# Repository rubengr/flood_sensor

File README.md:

# Flood Sensor 

## Pictures

## 3D

## Author
@2020
[Rúben Rodrigues](mailto:ruben_gr@live.com.pt)

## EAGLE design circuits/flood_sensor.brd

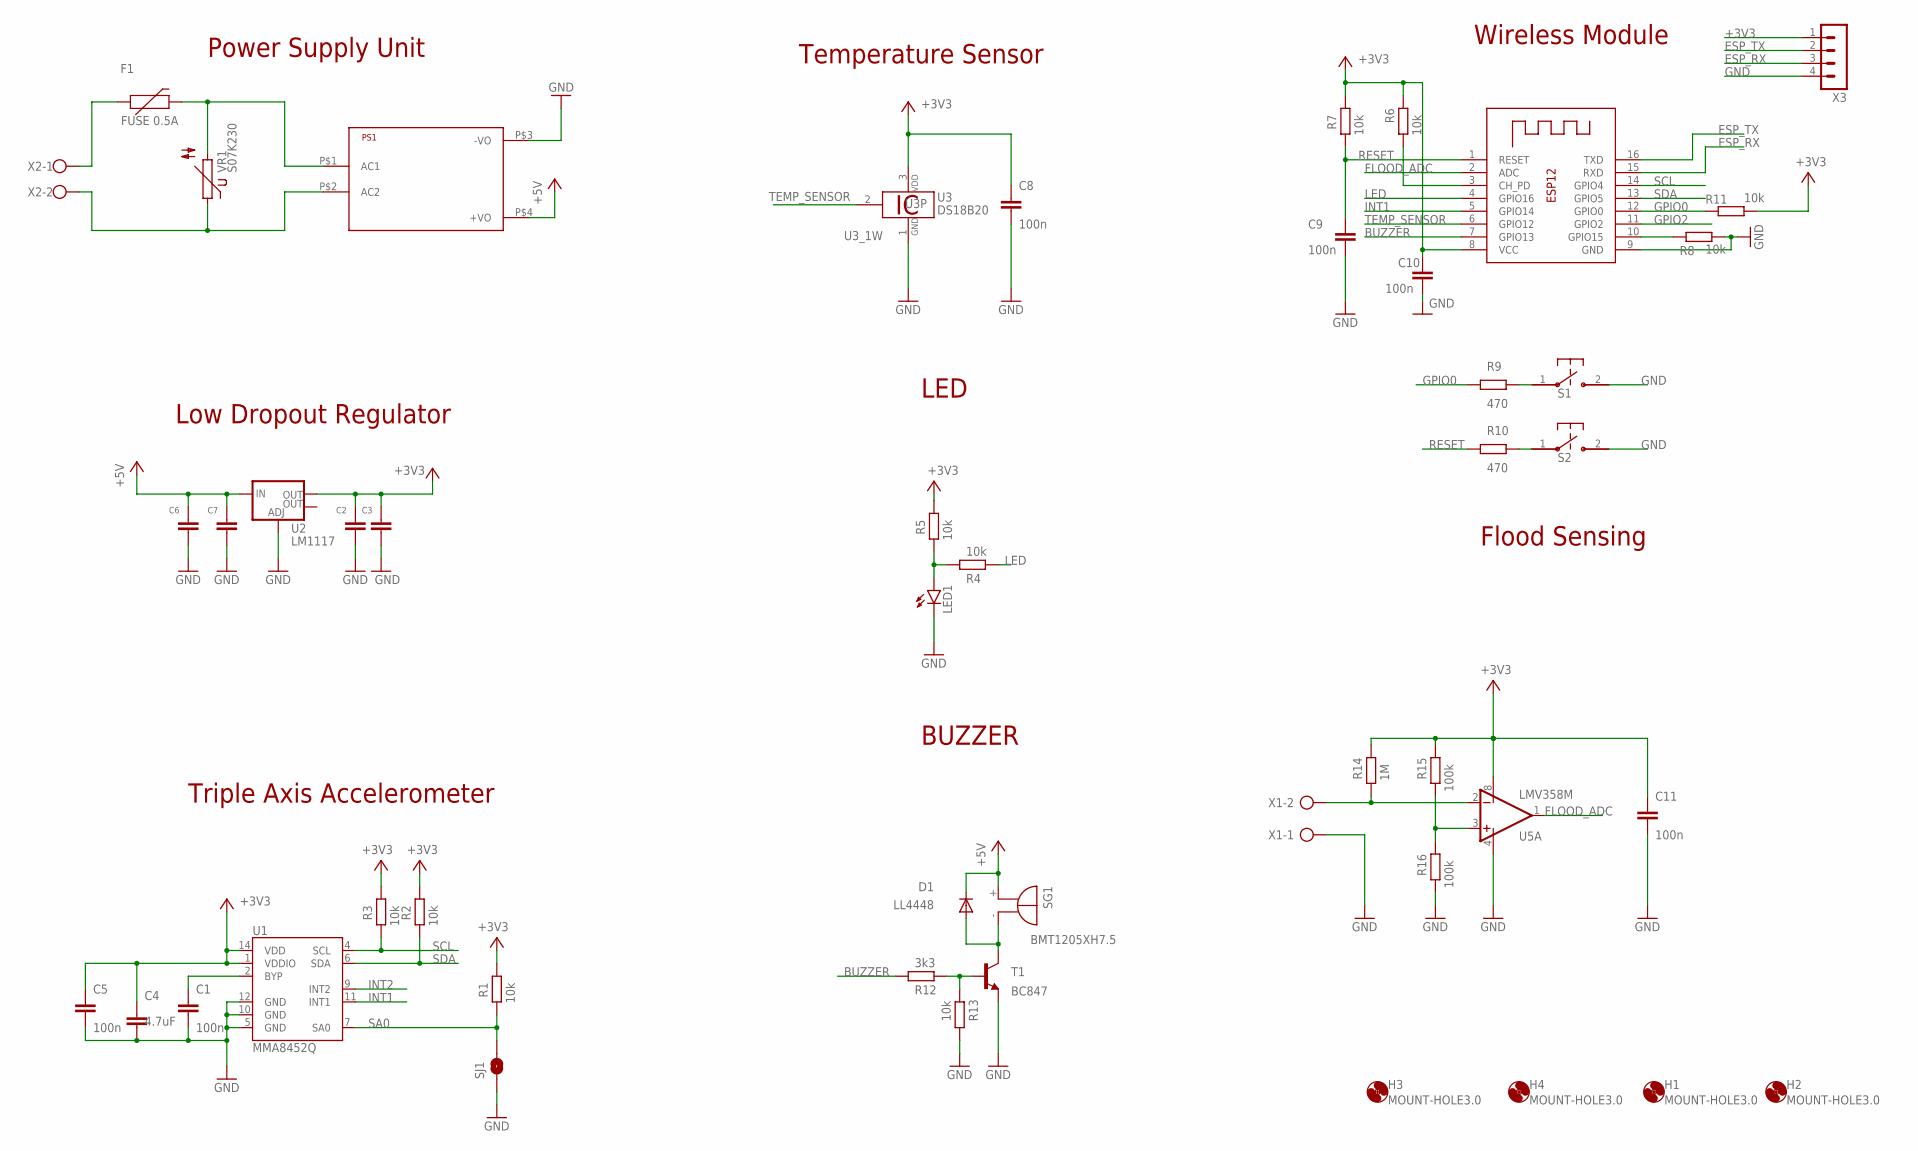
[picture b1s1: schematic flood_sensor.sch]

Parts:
C1, C5, C8, C9, C10, C11: 100n; C0805
C2, C7: 100uF; C1206
C3, C6: 22uF; C1206
C4: 4.7uF; C0805
D1: LL4448; SOD80C
F1: FUSE 0.5A; PTH
H1, H2, H3, H4: MOUNT-HOLE3.0; 3,0
LED1: LED3MM
PS1: HLK-PM013W; HLK-PM01
R1, R2, R3, R4, R5, R6, R7, R8, R11, R13: 10k; R0805
R9, R10: 470; R0805
R12: 3k3; R0805
R14: 1M; R0805
R15, R16: 100k; R0805
S1, S2: SWITCHES_B3U-1000P
SG1: BMT1205XH7.5
SJ1: SOLDERJUMPERNO; SJ_2S-NO
T1: BC847; SOT23
U1: MMA8452Q; QFN-16_0.5MM
U2: LM1117; SOT223
U3: DS18B20; TO92-
U4: ESP-12
U5: LMV358M; SO08
VR1: S07K230
X1, X2: W237-102
X3: MA04-1

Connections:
+3V3: C2.1, C3.1, C4.1, C5.1, C8.1, C10.1, C11.1, R1.1, R2.1, R3.1, R5.1, R6.1, R7.1, R11.2, R14.1, R15.1, U1.1 (VDDIO), U1.14 (VDD), U2.2 (OUT), U3.3 (VDD), U4.8 (VCC), U5.8 (V+), X3.1
+5V: C6.1, C7.1, D1.C, PS1.P$4 (+VO), SG1.+, U2.3 (IN)
BUZZER: R12.1, U4.7 (GPIO13)
BYP: C1.1, U1.2 (BYP)
ESP_RX: U4.15 (RXD), X3.3
ESP_TX: U4.16 (TXD), X3.2
FLOOD_ADC: U4.2 (ADC), U5.1 (OUT)
GND: C1.2, C2.2, C3.2, C4.2, C5.2, C6.2, C7.2, C8.2, C9.2, C10.2, C11.2, LED1.K (C), PS1.P$3 (-VO), R8.2, R13.1, R16.2, S1.2, S2.2, SJ1.1, T1.2 (E), U1.5 (GND), U1.10 (GND), U1.12 (GND), U2.1 (ADJ), U3.1 (GND), U4.9 (GND), U5.4 (V-), X1.1, X3.4
GPIO0: R9.1, R11.1, U4.12 (GPIO0)
GPIO2: U4.11 (GPIO2)
INT1: U1.11 (INT1), U4.5 (GPIO14)
INT2: U1.9 (INT2)
LED: R4.2, U4.4 (GPIO16)
unnamed: R8.1, U4.10 (GPIO15)
unnamed: R15.2, R16.1, U5.3 (+IN)
unnamed: F1.P$1 (1), X2.1
unnamed: F1.P$2 (2), PS1.P$1 (AC1), VR1.2
unnamed: PS1.P$2 (AC2), VR1.1, X2.2
unnamed: R9.2, S1.1
unnamed: LED1.A, R4.1, R5.2
unnamed: R14.2, U5.2 (-IN), X1.2
unnamed: R10.2, S2.1
unnamed: R6.2, U4.3 (CH_PD)
unnamed: D1.A, SG1.-, T1.3 (C)
unnamed: R12.2, R13.2, T1.1 (B)
RESET: C9.1, R7.2, R10.1, U4.1 (RESET)
SA0: R1.2, SJ1.2, U1.7 (SA0)
SCL: R3.2, U1.4 (SCL), U4.14 (GPIO4)
SDA: R2.2, U1.6 (SDA), U4.13 (GPIO5)
TEMP_SENSOR: U3.2 (1W), U4.6 (GPIO12)

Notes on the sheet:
Low Dropout Regulator
Power Supply Unit
Wireless Module
Flood Sensing
Triple Axis Accelerometer
Temperature Sensor
LED
BUZZER

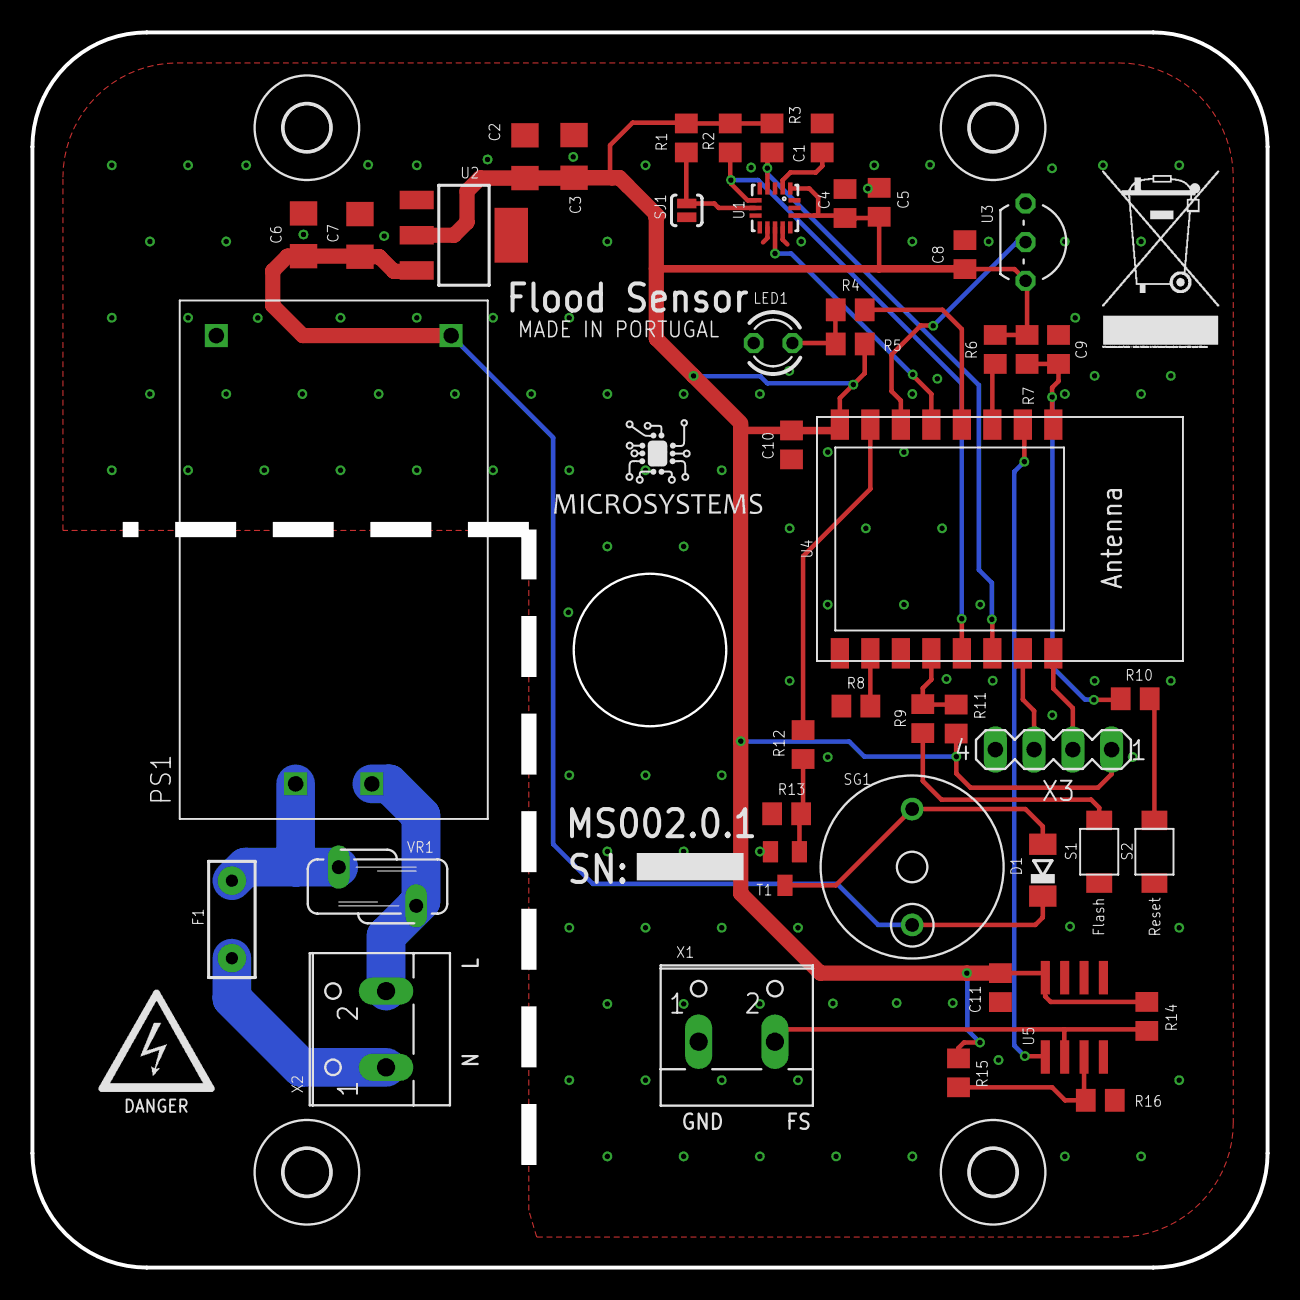
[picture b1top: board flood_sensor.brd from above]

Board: 2 copper layers, 80.3 x 80.3 mm, 52 parts (0 on the bottom side), 28 nets.

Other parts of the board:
U$1: DISPOSAL
U$2: LOGO
U$3: HIGH-VOLTAGE

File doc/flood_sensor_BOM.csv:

Qty;Value;Device;Package;Parts;Description;DIGIKEY;MANUFACTURER;MF;MPN;OC_FARNELL;OC_NEWARK;POPULARITY;PROD_ID;SERIE;SPICEPREFIX;VALUE
1;;ESP-12;ESP-12;U4;;;;;;;;;;;;
1;;LED3MM;LED3MM;LED1;LED;;;;;;;97;;;;
1;;MA04-1;MA04-1;X3;PIN HEADER;;;;;unknown;unknown;41;;;;
1;;SOLDERJUMPERNO;SJ_2S-NO;SJ1;Solder Jumper;;;;;;;;;;;
2;;W237-102;W237-102;X1, X2;WAGO SCREW CLAMP;;;;237-102;unknown;70K9898;32;;;;
2;100k;R-EU_R0805;R0805;R15, R16;RESISTOR, European symbol;;;;;;;86;;;R;
3;100n;C-EUC0805;C0805;C5, C8, C11;CAPACITOR, European symbol;;;;;;;88;;;C;
3;100n;C-EUC0805;C0805;C1, C9, C10;CAPACITOR, European symbol;;;;;;;;;;;
2;100uF;C-EUC1206;C1206;C2, C7;CAPACITOR, European symbol;;;;;;;54;;;C;
10;10k;R-EU_R0805;R0805;R1, R2, R3, R4, R5, R6, R7, R8, R11, R13;RESISTOR, European symbol;;;;;;;86;;;R;
1;1M;R-EU_R0805;R0805;R14;RESISTOR, European symbol;;;;;;;86;;;R;
2;22uF;C-EUC1206;C1206;C3, C6;CAPACITOR, European symbol;;;;;;;54;;;C;
1;3k3;R-EU_R0805;R0805;R12;RESISTOR, European symbol;;;;;;;86;;;R;
1;4.7uF;C-EUC0805;C0805;C4;CAPACITOR, European symbol;;;;;;;88;;;C;
2;470;R-EU_R0805;R0805;R9, R10;RESISTOR, European symbol;;;;;;;86;;;R;
1;BC847;BC847;SOT23;T1;NPN TRANSISTOR;;;;;;;;;;;
1;BMT1205XH7.5;BMT1205XH7.5;BMT1205XH7.5;SG1;MAGNETIC TRANSDUCER;;;;;unknown;unknown;0;;;;
1;DS18B20;DS18B20;TO92-;U3;Programmable Resolution Digital Thermometer;;;;;;;;;;;
1;FUSE 0.5A;PPTC_PTH;PTH;F1;Resettable Fuse PPTC;;;;;;;;RES-08490;392;;72V/0.25A
1;HLK-PM013W;HLK-PM013W;HLK-PM01;PS1;Hi-Link Power Supply;;;;;;;;;;;
1;LL4448;DIODE-SOD80C;SOD80C;D1;DIODE;;;;;;;;;;;
1;LM1117;V_REG_LM1117SOT223;SOT223;U2;Voltage Regulator LM1117;;;;;;;;VREG-08170;;;
1;LMV358M;LMV358M;SO08;U5;Dual General Purpose, Low Voltage, Rail-to-Rail Output Operational Amplifiers;;;;;;;0;;;;
1;MMA8452Q;MMA8452Q;QFN-16_0.5MM;U1;MMA8452Q 3-Axis, 12/8-bit Digital Accelerometer;;;;;;;;;;;
4;MOUNT-HOLE3.0;MOUNT-HOLE3.0;3;H1, H2, H3, H4;MOUNTING HOLE with drill center marker;;;;;;;3;;;;
1;S07K230;S07K230;S07K230;VR1;VARISTOR;;;;;;;0;;;;
2;SWITCHES_B3U-1000P;SWITCHES_B3U-1000P;SWITCHES_B3U-1000P;S1, S2;Switch;SW1020CT-ND;Omron;;B3U-1000P;;;;;;;

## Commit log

2020-04-13 added board layout
2020-04-13 remove copper close to outline
2020-04-20 Added rendered file
2020-04-23 updated flood_sensor
2020-05-06 corrected pcb dimensions
2020-06-17 finished first revision
2020-06-17 first version tag
2020-06-24 updated bom
2022-05-30 added code files
2022-08-01 Added code. Not working yet

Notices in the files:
parts and their libraries:
SparkFun-Fuses: Licensing: Creative Commons ShareAlike 4.0 International - https://creativecommons.org/licenses/by-sa/4.0
ruben: MIT License
Copyright (c) 2020 MicroSystems
